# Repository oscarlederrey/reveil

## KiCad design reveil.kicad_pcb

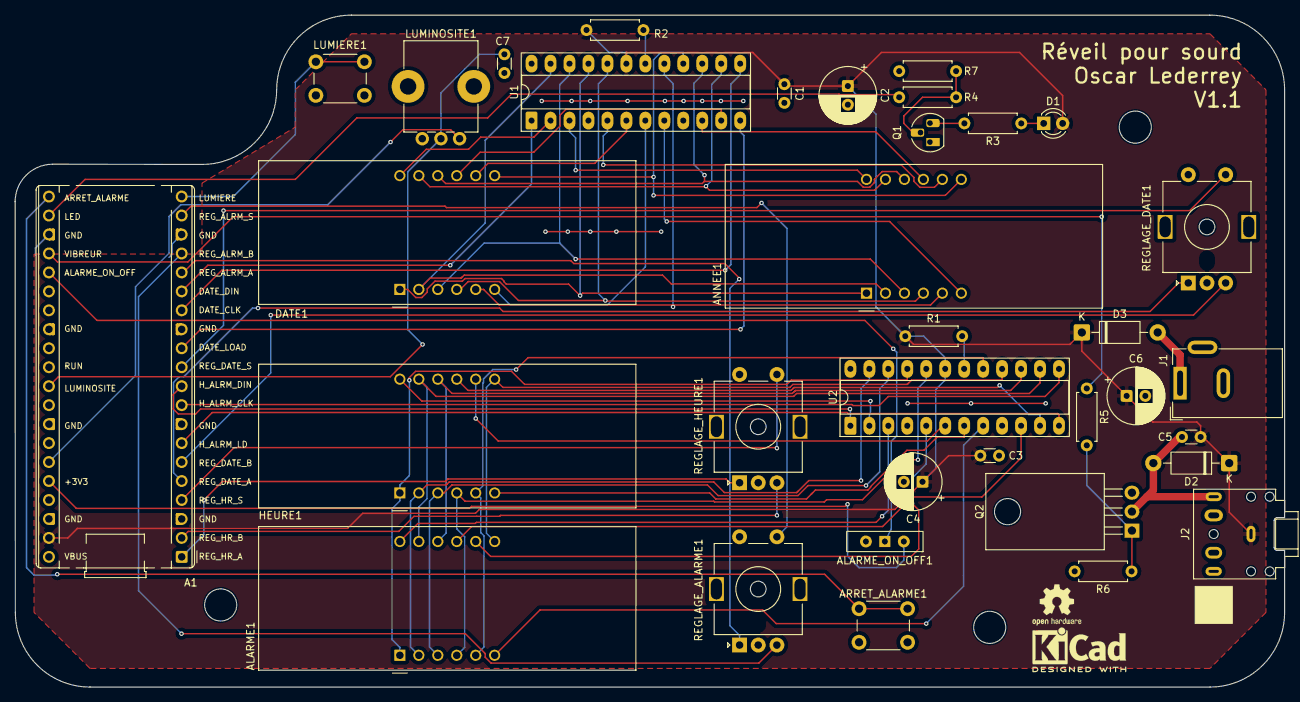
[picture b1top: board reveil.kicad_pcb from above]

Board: 2 copper layers, 170.0 x 89.9 mm, 38 parts (0 on the bottom side), 65 nets.

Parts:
A1: RaspberryPi_Pico_W; RaspberryPi_Pico_Common_THT
ALARME1: CC56-12EWA; CA56-12EWA
ALARME_ON_OFF1: SW_SPDT; SW_Slide-03_Wuerth-WS-SLTV_10x2.5x6.4_P2.54mm
ANNEE1: CC56-12EWA; CA56-12EWA
ARRET_ALARME1: SW_Push; SW_PUSH_6mm
C1, C3: 100nF; C_Disc_D3.0mm_W1.6mm_P2.50mm
C2, C4: 10uF; CP_Radial_D7.5mm_P2.50mm
C5, C7: 100n; C_Disc_D3.0mm_W1.6mm_P2.50mm
C6: 220uF; CP_Radial_D7.5mm_P2.50mm
D1: LED; LED_D3.0mm
D2, D3: 1N5822; D_DO-41_SOD81_P10.16mm_Horizontal
DATE1: CC56-12EWA; CA56-12EWA
H1, H2, H3: MountingHole; MountingHole_4.3mm_M4
HEURE1: CC56-12EWA; CA56-12EWA
J1: Barrel_Jack_Switch; BarrelJack_Wuerth_6941xx301002
J2: AudioJack3_SwitchTR; Jack_3.5mm_CUI_SJ1-3525N_Horizontal
LUMIERE1: SW_Push; SW_PUSH_6mm
LUMINOSITE1: R_Potentiometer_MountingPin; Potentiometer_Bourns_PTV09A-1_Single_Vertical
Q1: 2N3904; TO-92_HandSolder
Q2: IRLB8721PBF; TO-220-3_Horizontal_TabDown
R1, R2, R7: 47K; R_Axial_DIN0207_L6.3mm_D2.5mm_P7.62mm_Horizontal
R3: 100; R_Axial_DIN0207_L6.3mm_D2.5mm_P7.62mm_Horizontal
R4: 1.5K; R_Axial_DIN0207_L6.3mm_D2.5mm_P7.62mm_Horizontal
R5: 100R; R_Axial_DIN0207_L6.3mm_D2.5mm_P7.62mm_Horizontal
R6: 100k; R_Axial_DIN0207_L6.3mm_D2.5mm_P7.62mm_Horizontal
REGLAGE_ALARME1: RotaryEncoder_Switch_MP; RotaryEncoder_Alps_EC11E-Switch_Vertical_H20mm_MountingHoles
REGLAGE_DATE1: RotaryEncoder_Switch_MP; RotaryEncoder_Alps_EC11E-Switch_Vertical_H20mm_MountingHoles
REGLAGE_HEURE1: RotaryEncoder_Switch_MP; RotaryEncoder_Alps_EC11E-Switch_Vertical_H20mm_MountingHoles
U1, U2: MAX7219; DIP-24_W7.62mm_Socket_LongPads

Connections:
+3V3: A1.36 (3V3), ALARME_ON_OFF1.1 (A)
ADC_VREF: A1.35 (ADC_VREF), LUMINOSITE1.1
ALARME_ON_OFF: A1.25 (GPIO19), ALARME_ON_OFF1.2 (B)
ARRET_ALARME: A1.21 (GPIO16), ARRET_ALARME1.1
DATE_CLK: A1.14 (GPIO10), U1.13 (CLK)
DATE_DIN: A1.15 (GPIO11), U1.1 (DIN)
DATE_LOAD: A1.12 (GPIO9), U1.12 (LOAD)
GND: A1.3 (GND), A1.8 (GND), A1.13 (GND), A1.18 (GND), A1.23 (GND), A1.28 (GND), A1.33 (AGND), A1.38 (GND), ALARME_ON_OFF1.3 (C), ARRET_ALARME1.2, C1.2, C2.2, C3.2, C4.2, C6.2, C7.2, J1.2, LUMIERE1.2, LUMINOSITE1.3, LUMINOSITE1.MP (MountPin), Q1.1 (E), Q2.3 (S), R6.2, R7.2, REGLAGE_ALARME1.C, REGLAGE_ALARME1.MP, REGLAGE_ALARME1.S2, REGLAGE_DATE1.C, REGLAGE_DATE1.MP, REGLAGE_DATE1.S2, REGLAGE_HEURE1.C, REGLAGE_HEURE1.MP, REGLAGE_HEURE1.S2, U1.4 (GND), U1.9 (GND), U2.4 (GND), U2.9 (GND)
HEURE_ALARME_CLK: A1.9 (GPIO6), U2.13 (CLK)
HEURE_ALARME_DIN: A1.10 (GPIO7), U2.1 (DIN)
HEURE_ALARME_LOAD: A1.7 (GPIO5), U2.12 (LOAD)
LED: A1.22 (GPIO17), R4.1
LUMIERE: A1.20 (GPIO15), LUMIERE1.1
LUMINOSITE: A1.31 (GPIO26_ADC0), C7.1, LUMINOSITE1.2
unnamed: ALARME1.12 (CC1), U2.3 (DIG_4)
unnamed: ALARME1.9 (CC2), U2.10 (DIG_5)
unnamed: ALARME1.8 (CC3), U2.5 (DIG_6)
unnamed: ALARME1.6 (CC4), U2.8 (DIG_7)
unnamed: ALARME1.3 (DPX), HEURE1.3 (DPX), U2.22 (SEG_DP)
unnamed: ALARME1.11 (a), HEURE1.11 (a), U2.14 (SEG_A)
unnamed: ALARME1.7 (b), HEURE1.7 (b), U2.16 (SEG_B)
unnamed: ALARME1.4 (c), HEURE1.4 (c), U2.20 (SEG_C)
unnamed: ALARME1.2 (d), HEURE1.2 (d), U2.23 (SEG_D)
unnamed: ALARME1.1 (e), HEURE1.1 (e), U2.21 (SEG_E)
unnamed: ALARME1.10 (f), HEURE1.10 (f), U2.15 (SEG_F)
unnamed: ALARME1.5 (g), HEURE1.5 (g), U2.17 (SEG_G)
unnamed: ANNEE1.12 (CC1), U1.3 (DIG_4)
unnamed: ANNEE1.9 (CC2), U1.10 (DIG_5)
unnamed: ANNEE1.8 (CC3), U1.5 (DIG_6)
unnamed: ANNEE1.6 (CC4), U1.8 (DIG_7)
unnamed: ANNEE1.3 (DPX), DATE1.3 (DPX), U1.22 (SEG_DP)
unnamed: ANNEE1.11 (a), DATE1.11 (a), U1.14 (SEG_A)
unnamed: ANNEE1.7 (b), DATE1.7 (b), U1.16 (SEG_B)
unnamed: ANNEE1.4 (c), DATE1.4 (c), U1.20 (SEG_C)
unnamed: ANNEE1.2 (d), DATE1.2 (d), U1.23 (SEG_D)
unnamed: ANNEE1.1 (e), DATE1.1 (e), U1.21 (SEG_E)
unnamed: ANNEE1.10 (f), DATE1.10 (f), U1.15 (SEG_F)
unnamed: ANNEE1.5 (g), DATE1.5 (g), U1.17 (SEG_G)
unnamed: D1.1 (K), R3.1
unnamed: C5.2, D2.2 (A), J2.T, Q2.2 (D)
unnamed: D3.2 (A), J1.1
unnamed: DATE1.12 (CC1), U1.2 (DIG_0)
unnamed: DATE1.9 (CC2), U1.11 (DIG_1)
unnamed: DATE1.8 (CC3), U1.6 (DIG_2)
unnamed: DATE1.6 (CC4), U1.7 (DIG_3)
unnamed: HEURE1.12 (CC1), U2.2 (DIG_0)
unnamed: HEURE1.9 (CC2), U2.11 (DIG_1)
unnamed: HEURE1.8 (CC3), U2.6 (DIG_2)
unnamed: HEURE1.6 (CC4), U2.7 (DIG_3)
unnamed: Q1.2 (B), R4.2, R7.1
unnamed: Q1.3 (C), R3.2
unnamed: Q2.1 (G), R5.2, R6.1
unnamed: R2.2, U1.18 (ISET)
unnamed: R1.2, U2.18 (ISET)
REGLAGE_ALARME_A: A1.16 (GPIO12), REGLAGE_ALARME1.A
REGLAGE_ALARME_B: A1.17 (GPIO13), REGLAGE_ALARME1.B
REGLAGE_ALARME_S: A1.19 (GPIO14), REGLAGE_ALARME1.S1
REGLAGE_DATE_A: A1.5 (GPIO3), REGLAGE_DATE1.A
REGLAGE_DATE_B: A1.6 (GPIO4), REGLAGE_DATE1.B
REGLAGE_DATE_S: A1.11 (GPIO8), REGLAGE_DATE1.S1
REGLAGE_HEURE_A: A1.1 (GPIO0), REGLAGE_HEURE1.A
REGLAGE_HEURE_B: A1.2 (GPIO1), REGLAGE_HEURE1.B
REGLAGE_HEURE_S: A1.4 (GPIO2), REGLAGE_HEURE1.S1
VIBREUR: A1.24 (GPIO18), R5.1
VSYS: A1.39 (VSYS), C1.1, C2.1, C3.1, C4.1, C5.1, C6.1, D1.2 (A), D2.1 (K), D3.1 (K), J2.S, R1.1, R2.1, U1.19 (V+), U2.19 (V+)

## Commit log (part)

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2026-02-17 added ground to rotary encoders
2026-02-17 added 3V3
